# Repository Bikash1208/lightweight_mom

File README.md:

# HMSA Designer & RIS Metasurface Toolkit (`lwmom`)

A Python periodic Method-of-Moments solver for metasurface unit cells, plus a local web app ("HMSA Designer"):
- **HMSA Design:** Design holographic and reflectarray metasurface antennas end to end: upload a monopole feed's measured surface-wave field, configure multi-port beams and board geometry, synthesize holograms with sidelobe optimisation, predict far-field patterns, and export HFSS-ready CAD and AEDT scripts.
- **RIS Track (Phase 20):** Design 2-bit PIN-diode reconfigurable intelligent surfaces at X-band (10.5 GHz CP-2 Pancharatnam–Berry cell family and 1-bit LP interim), with plane-wave beam steering, coding synthesis, diode tolerance modeling, and board export.

Read **[docs/START_HERE.md](docs/START_HERE.md)** first — purpose, design flow, repo map,
conventions that bite.
Then **[docs/ROADMAP.md](docs/ROADMAP.md)** for deliverables, completed phases, and active track.
Check **[docs/STATUS.md](docs/STATUS.md)** for what's validated right now.

## Install and run

```bash
python3 --version                   # must be >= 3.11 -- if not, substitute your 3.11+
                                     # interpreter below (e.g. python3.12, python3.14, pyenv's)
python3 -m venv .venv && source .venv/bin/activate
pip install -e ".[dev,app,cad]"     # dev: tests/lint; app: the web app; cad: STEP export/plots
make app                            # starts the app at http://127.0.0.1:8000 -- restart after
                                     # any backend (src/) change, there is no autoreload
make test-fast                      # pytest -m "not slow", ~6-7 min
make test-full                      # everything, including real MoM solves, tens of minutes
make lint / make format             # ruff check(+format) / ruff check --fix + format
```

Python >= 3.11. `requirements-lock.txt` reproduces the exact pinned environment this project was
developed against (`pip install -r requirements-lock.txt`). See `docs/DEVELOPING.md` for the full
setup/test/lint walkthrough and `docs/ARCHITECTURE.md` for how the app is put together.

## More

- [docs/START_HERE.md](docs/START_HERE.md) — onboarding (humans and AI agents).
- [docs/ROADMAP.md](docs/ROADMAP.md) — planned deliverables, completed phases, and active milestones.
- [docs/STATUS.md](docs/STATUS.md) — current validation level per capability, open next steps.
- [docs/USER_GUIDE.md](docs/USER_GUIDE.md) — walkthrough of every app page.
- [docs/ARCHITECTURE.md](docs/ARCHITECTURE.md) — module map, data flow, job queue, storage.
- [docs/validation/README.md](docs/validation/README.md) — every validation run, with numbers.
- [docs/history/](docs/history/) — the full phase-by-phase project history.
- [jobs/README.md](jobs/README.md) — remote compute server job architecture and status matrix.
- [hfss_results/README.md](hfss_results/README.md) — external HFSS simulation runs and ground-truth data.
- [CHANGELOG.md](CHANGELOG.md), [CONTRIBUTING.md](CONTRIBUTING.md), [CLAUDE.md](CLAUDE.md).

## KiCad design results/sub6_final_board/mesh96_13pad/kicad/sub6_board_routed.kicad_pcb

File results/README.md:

# Results

Generated outputs, one folder per phase/script. Tracked research outputs (small
JSON/CSV/MD/plots/STEP) stay in git as the project's own record; a few genuinely heavy, fully
regenerable folders are gitignored (noted below).

| Folder | Produced by | Regenerate with |
|---|---|---|
| `phase8a_feasibility/` | Phase 8A feasibility gate | `scripts/research/run_phase8a_feasibility.py` |
| `phase8b_formulation/` | Phase 8B holographic formulation | `scripts/research/run_phase8b_formulation.py` |
| `phase8c_scattering/` | Phase 8C scattering architecture validation | `scripts/research/run_phase8c_validation.py` |
| `phase8e_control_bridge/` | Phase 8E control-variable bridge | `scripts/research/run_phase8e_control_bridge.py` |
| `phase9_validation/` | Phase 9 control-variable/local-periodicity validation | `scripts/research/run_phase9_validation.py` |
| `phase10_environment_model/` | Phase 10 environment-aware model | `scripts/research/run_phase10_environment_model.py` |
| `phase11_heterogeneous_mom/` | Phase 11 heterogeneous-MoM coupling study | `scripts/research/run_phase11_heterogeneous_mom.py` |
| `phase12a_ground_plane/` | Phase 12A PEC ground plane | `scripts/research/run_phase12a_ground_plane.py` |
| `phase12b_mesh_period_study/` | Phase 12B mesh/period study | `scripts/research/run_phase12b.py` |
| `phase12c_grounded_locality/`, `phase12c_hfss_export/` | Phase 12C grounded-supercell study + HFSS exports | `scripts/research/run_phase12c.py` |
| `phase12d_local_periodicity/` | Phase 12D step-limit + HFSS ingestion | `scripts/research/run_phase12d.py` |
| `phase13_part0/` | Phase 13 Part 0 carry-overs | `scripts/research/run_phase13_part0.py` |
| `validation_cases/` | Phase 6 STEP/JSON/CSV validation-case exports | `scripts/research/export_validation_cases.py` |
| `unit_cell_library/` | Phase 7 production unit-cell library | `examples/build_unit_cell_library.py` (long-running, resumable). **Gitignored**: `_solve/`, `database/`, `geometry/` (~554 MB) — only `manifest.json`/reports/plots are committed. |
| `nylon_cells_28ghz/` | Phase 19 Part B: 28 GHz nylon octagon cell library (RCWA, model-only) | `examples/build_nylon_cell_library_28ghz.py` (~3 min) |
| `transmitarray_dual30/` | Phase 19 Parts C-D: dual-beam ±30° nylon lens design, local-periodicity and error-bar records (model-only) | `scripts/research/phase19_design.py` (~15 min), then `phase19_local_periodicity.py` (~10 min); see its README |
| `phase20_r1_demo/` | Phase 20 R1: Oblique-incidence and lumped-load MoM demo outputs and convergence checks | `scripts/research/phase20_r1_demo.py` |
| `phase20_r2/` | Phase 20 R2: PIN diode circuit models (Skyworks SMP1345-079LF) and bias-dependent reflection sweeps | `scripts/research/phase20_r2_demo.py` |
| `phase20_r3/` | Phase 20 R3: 2-bit Pancharatnam-Berry octagon unit cell (CP-2) optimization, 4-state phase ladder, and supercell locality data | `scripts/research/phase20_r3_cp_package.py`, `scripts/research/phase20_r3_opt.py`, `scripts/research/phase20_r3_locality.py` |
| `phase20_r3b/` | Phase 20 R3b: Re-optimization study outcome; baseline CP-2 cell retained, optimisation stopped (`OUTCOME.md`) | `scripts/research/phase20_r3b_cp_package.py` |
| `phase20_r4/` | Phase 20 R4: Discrete state library (v1 and full-grid v2 at Floquet cutoff F = 2n = 120), cutoff audit, and HFSS compare plots. **Gitignored**: `chunks/` | `scripts/research/phase20_r4_build_library.py`, `scripts/research/phase20_r4_assemble.py`, `scripts/research/phase20_r4_hfss_compare.py` |
| `phase20_r5/` | Phase 20 R5: RIS design mode records, reference-plane calibration (`PLANE_CORRECTION.md`), R5-3 beam tables (`R5_3_REPORT.md`), and server MoM tolerance analysis (`TOLERANCE_GAP.md`) | `scripts/research/phase20_r5_rebuild_delta.py`, `scripts/research/phase20_r5_tolerance_mom.py`, `scripts/research/phase20_r5_tolerance_compare.py` |
| `phase23/` | Phase 23: square vs hexagon vs hexagon + sidelobe optimiser comparison on the held-out grid; the rectangle bit-identical gate | `scripts/research/phase23_compare_v2.py`; gate `scripts/research/phase23_rect_snapshot.py` |
| `phase25/` | Phase 25: Butler-fed sector scanner forward model (`forward_validation.json`), supercell locality checks, and aperture-taper sensitivity (model-only) | `scripts/research/phase25_forward_validation.py`, `scripts/research/phase25_locality_package.py`, `scripts/research/phase25_block_locality.py` |
| `phase26/` | Phase 26: Leakage-controlled tensor-CP hexagon design (`fourhex_A_cells.json`, `fourhex_B_cells.json`), launcher calibration, and substrate screening tables | `scripts/research/phase26_fourhex_design.py`, `scripts/research/phase26_launcher_package.py`, `scripts/research/phase26_substrate_study.py` |
| `infra/` | Server sync provenance records, mirror checks, and cross-machine equivalence artifacts | `scripts/research/equivalence_compare.py`, `scripts/research/phase20_r4_mirror_check.py` |
| `universal_database/` | Phase 8D-REV universal database architecture demo | `scripts/research/run_phase8d_rev_universal_database.py` |
| `hfss_compare_ledger.json` (not a folder) | Every HFSS-vs-MoM comparison run through the app's HFSS compare page | append-only; see `src/hfss_compare/service.py` |
| `submission_work/` | **Untracked scratch** (Oct 5–6 2026), not part of the repo | its reusable scripts moved to `scripts/adhoc/` in Phase 17; see that folder's own README |

Tests that read any of the folders above treat them as read-only fixtures/benchmarks — do not
hand-edit a results file to make a test pass; fix the generator or the test.

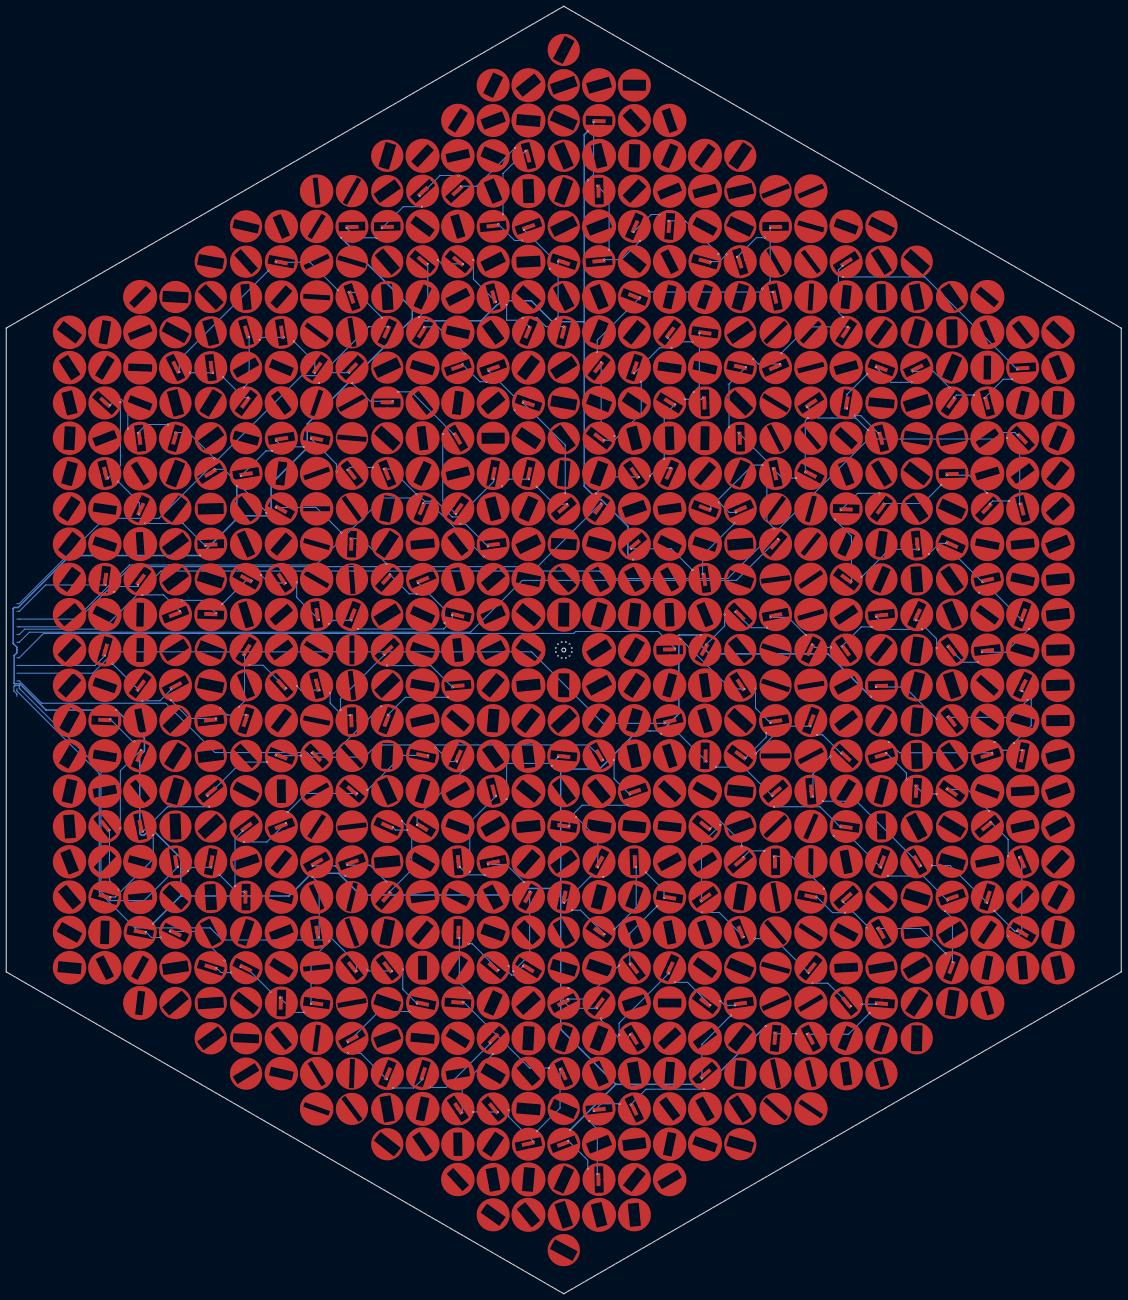
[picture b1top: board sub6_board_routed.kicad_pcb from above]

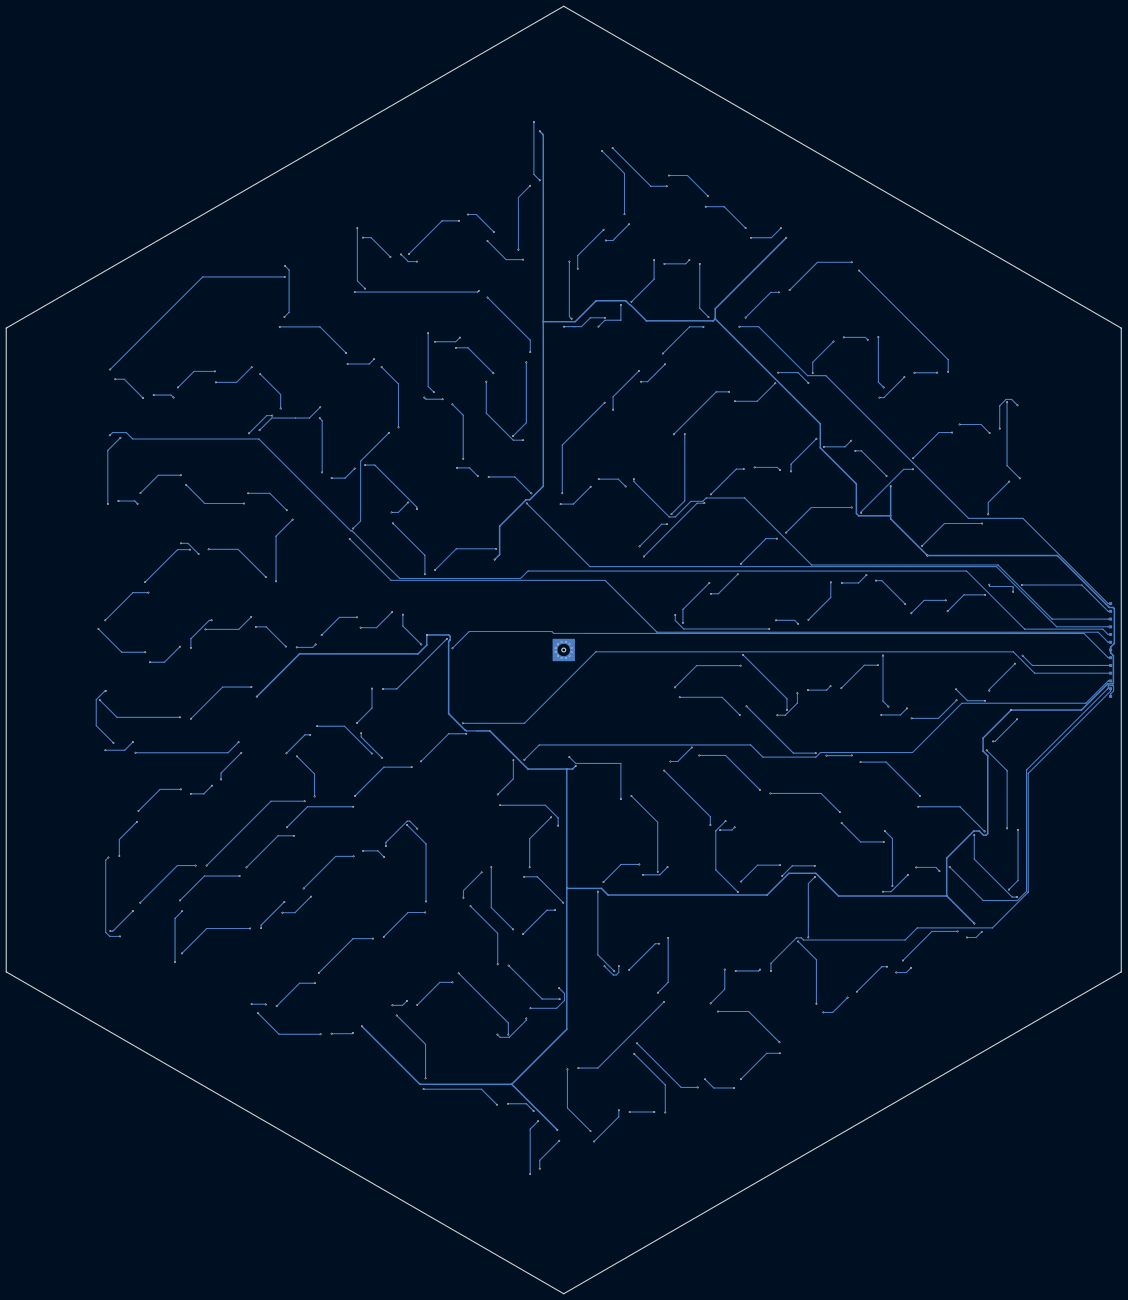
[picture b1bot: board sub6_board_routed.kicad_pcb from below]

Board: 4 copper layers, 366.4 x 423.1 mm, 1001 parts (2 on the bottom side), 241 nets.

Parts:
C0, C1, C2, C3, C4, C5, C6, C7, C8, C9, C10, C11, C12, C13, C14, C15, C16, C17, C18, C19, C20, C21, C22, C23, C24, C25, C26, C27, C28, C29, C30, C31, C32, C33, C34, C35, C36, C37, C38, C39, C40, C41, C42, C43, C44, C45, C46, C47, C48, C49, C50, C51, C52, C53, C54, C55, C56, C57, C58, C59, C60, C61, C62, C63, C64, C65, C66, C67, C68, C69, C70, C71, C72, C73, C74, C75, C76, C77, C78, C79, C80, C81, C82, C83, C84, C85, C86, C87, C88, C89, C90, C91, C92, C93, C94, C95, C96, C97, C98, C99, C100, C101, C102, C103, C104, C105, C106, C107, C108, C109, C110, C111, C112, C113, C114, C115, C116, C117, C118, C119, C120, C121, C122, C123, C124, C125, C126, C127, C128, C129, C130, C131, C132, C133, C134, C135, C136, C137, C138, C139, C140, C141, C142, C143, C144, C145, C146, C147, C148, C149, C150, C151, C152, C153, C154, C155, C156, C157, C158, C159, C160, C161, C162, C163, C164, C165, C166, C167, C168, C169, C170, C171, C172, C173, C174, C175, C176, C177, C178, C179, C180, C181, C182, C183, C184, C185, C186, C187, C188, C189, C190, C191, C192, C193, C194, C195, C196, C197, C198, C199, C200, C201, C202, C203, C204, C205, C206, C207, C208, C209, C210, C211, C212, C213, C214, C215, C216, C217, C218, C219, C220, C221, C222, C223, C224, C225, C226, C227, C228, C229, C230, C231, C232, C233, C234, C235, C236, C237, C238, C239, C240, C241, C242, C243, C244, C245, C246, C247, C248, C249, C250, C251, C252, C253, C254, C255, C256, C257, C258, C259, C260, C261, C262, C263, C264, C265, C266, C267, C268, C269, C270, C271, C272, C273, C274, C275, C276, C277, C278, C279, C280, C281, C282, C283, C284, C285, C286, C287, C288, C289, C290, C291, C292, C293, C294, C295, C296, C297, C298, C299, C300, C301, C302, C303, C304, C305, C306, C307, C308, C309, C310, C311, C312, C313, C314, C315, C316, C317, C318, C319, C320, C321, C322, C323, C324, C325, C326, C327, C328, C329, C330, C331, C332, C333, C334, C335, C336, C337, C338, C339, C340, C341, C342, C343, C344, C345, C346, C347, C348, C349, C350, C351, C352, C353, C354, C355, C356, C357, C358, C359, C360, C361, C362, C363, C364, C365, C366, C367, C368, C369, C370, C371, C372, C373, C374, C375, C376, C377, C378, C379, C380, C381, C382, C383, C384, C385, C386, C387, C388, C389, C390, C391, C392, C393, C394, C395, C396, C397, C398, C399, C400, C401, C402, C403, C404, C405, C406, C407, C408, C409, C410, C411, C412, C413, C414, C415, C416, C417, C418, C419, C420, C421, C422, C423, C424, C425, C426, C427, C428, C429, C430, C431, C432, C433, C434, C435, C436, C437, C438, C439, C440, C441, C442, C443, C444, C445, C446, C447, C448, C449, C450, C451, C452, C453, C454, C455, C456, C457, C458, C459, C460, C461, C462, C463, C464, C465, C466, C467, C468, C469, C470, C471, C472, C473, C474, C475, C476, C477, C478, C479, C480, C481, C482, C483, C484, C485, C486, C487, C488, C489, C490, C491, C492, C493, C494, C495, C496, C497, C498, C499, C500, C501, C502, C503, C504, C505, C506, C507, C508, C509, C510, C511, C512, C513, C514, C515, C516, C517, C518, C519, C520, C521, C522, C523, C524, C525, C526, C527, C528, C529, C530, C531, C532, C533, C534, C535, C536, C537, C538, C539, C540, C541, C542, C543, C544, C545, C546, C547, C548, C549, C550, C551, C552, C553, C554, C555, C556, C557, C558, C559, C560, C561, C562, C563, C564, C565, C566, C567, C568, C569, C570, C571, C572, C573, C574, C575, C576, C577, C578, C579, C580, C581, C582, C583, C584, C585, C586, C587, C588, C589, C590, C591, C592, C593, C594, C595, C596, C597, C598, C599, C600, C601, C602, C603, C604, C605, C606, C607, C608, C609, C610, C611, C612, C613, C614, C615, C616, C617, C618, C619, C620, C621, C622, C623, C624, C625, C626, C627, C628, C629, C630, C631, C632, C633, C634, C635, C636, C637, C638, C639, C640, C641, C642, C643, C644, C645, C646, C647, C648, C649, C650, C651, C652, C653, C654, C655, C656, C657, C658, C659, C660, C661, C662, C663, C664, C665, C666, C667, C668, C669, C670, C671, C672, C673, C674, C675, C676, C677, C678, C679, C680, C681, C682, C683, C684, C685, C686, C687, C688, C689, C690, C691, C692, C693, C694, C695, C696, C697, C698, C699, C700, C701, C702, C703, C704, C705, C706, C707, C708, C709, C710, C711, C712, C713, C714, C715, C716, C717, C718, C719, C720, C721, C722, C723, C724, C725, C726, C727, C728, C729, C730, C731, C732, C733, C734, C735, C736, C737, C738, C739, C740, C741, C742, C743, C744, C745, C746, C747, C748, C749, C750, C751, C752, C753, C754, C755, C756, C757: CELL
D1-01, D1-02, D1-03, D1-04, D1-05, D1-06, D1-07, D1-08, D1-09, D1-10, D1-11, D1-12, D1-13, D1-14, D1-15, D1-16, D1-17, D1-18, D1-19, D1-20, D2-01, D2-02, D2-03, D2-04, D2-05, D2-06, D2-07, D2-08, D2-09, D2-10, D2-11, D2-12, D2-13, D2-14, D2-15, D2-16, D2-17, D2-18, D2-19, D2-20, D3-01, D3-02, D3-03, D3-04, D3-05, D3-06, D3-07, D3-08, D3-09, D3-10, D3-11, D3-12, D3-13, D3-14, D3-15, D3-16, D3-17, D3-18, D3-19, D3-20, D4-01, D4-02, D4-03, D4-04, D4-05, D4-06, D4-07, D4-08, D4-09, D4-10, D4-11, D4-12, D4-13, D4-14, D4-15, D4-16, D4-17, D4-18, D4-19, D4-20, D5-01, D5-02, D5-03, D5-04, D5-05, D5-06, D5-07, D5-08, D5-09, D5-10, D5-11, D5-12, D5-13, D5-14, D5-15, D5-16, D5-17, D5-18, D5-19, D5-20, D6-01, D6-02, D6-03, D6-04, D6-05, D6-06, D6-07, D6-08, D6-09, D6-10, D6-11, D6-12, D6-13, D6-14, D6-15, D6-16, D6-17, D6-18, D6-19, D6-20, D7-01, D7-02, D7-03, D7-04, D7-05, D7-06, D7-07, D7-08, D7-09, D7-10, D7-11, D7-12, D7-13, D7-14, D7-15, D7-16, D7-17, D7-18, D7-19, D7-20, D8-01, D8-02, D8-03, D8-04, D8-05, D8-06, D8-07, D8-08, D8-09, D8-10, D8-11, D8-12, D8-13, D8-14, D8-15, D8-16, D8-17, D8-18, D8-19, D8-20, D9-01, D9-02, D9-03, D9-04, D9-05, D9-06, D9-07, D9-08, D9-09, D9-10, D9-11, D9-12, D9-13, D9-14, D9-15, D9-16, D9-17, D9-18, D9-19, D9-20, D10-01, D10-02, D10-03, D10-04, D10-05, D10-06, D10-07, D10-08, D10-09, D10-10, D10-11, D10-12, D10-13, D10-14, D10-15, D10-16, D10-17, D10-18, D10-19, D10-20, D11-01, D11-02, D11-03, D11-04, D11-05, D11-06, D11-07, D11-08, D11-09, D11-10, D11-11, D11-12, D11-13, D11-14, D11-15, D11-16, D11-17, D11-18, D11-19, D11-20, D12-01, D12-02, D12-03, D12-04, D12-05, D12-06, D12-07, D12-08, D12-09, D12-10, D12-11, D12-12, D12-13, D12-14, D12-15, D12-16, D12-17, D12-18, D12-19, D12-20: SC79
J1: EDGE_CONN13
J2: SMA_FLAT_PAD_6.35
P1: PROBE

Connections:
N01_01: C338.2, C366.1, D1-01.K, D1-02.A
N01_02: C338.1, C339.2, D1-02.K, D1-03.A
N01_03: C311.2, C339.1, D1-03.K, D1-04.A
N01_04: C311.1, C312.2, D1-04.K, D1-05.A
N01_05: C312.1, C370.2, D1-05.K, D1-06.A
N01_06: C342.2, C370.1, D1-06.K, D1-07.A
N01_07: C342.1, C343.2, D1-07.K, D1-08.A
N01_08: C315.2, C343.1, D1-08.K, D1-09.A
N01_09: C315.1, C374.2, D1-09.K, D1-10.A
N01_10: C347.2, C374.1, D1-10.K, D1-11.A
N01_11: C316.2, C347.1, D1-11.K, D1-12.A
N01_12: C285.2, C316.1, D1-12.K, D1-13.A
N01_13: C284.2, C285.1, D1-13.K, D1-14.A
N01_14: C253.2, C284.1, D1-14.K, D1-15.A
N01_15: C222.2, C253.1, D1-15.K, D1-16.A
N01_16: C163.2, C222.1, D1-16.K, D1-17.A
N01_17: C163.1, C221.2, D1-17.K, D1-18.A
N01_18: C221.1, C280.2, D1-18.K, D1-19.A
N01_19: C280.1, C308.2, D1-19.K, D1-20.A
N02_01: C194.1, C195.2, D2-01.K, D2-02.A
N02_02: C167.2, C195.1, D2-02.K, D2-03.A
N02_03: C167.1, C225.2, D2-03.K, D2-04.A
N02_04: C225.1, C226.2, D2-04.K, D2-05.A
N02_05: C226.1, C257.2, D2-05.K, D2-06.A
N02_06: C257.1, C288.2, D2-06.K, D2-07.A
N02_07: C288.1, C289.2, D2-07.K, D2-08.A
N02_08: C230.2, C289.1, D2-08.K, D2-09.A
N02_09: C229.2, C230.1, D2-09.K, D2-10.A
N02_10: C171.2, C229.1, D2-10.K, D2-11.A
N02_11: C171.1, C199.2, D2-11.K, D2-12.A
N02_12: C198.2, C199.1, D2-12.K, D2-13.A
N02_13: C140.2, C198.1, D2-13.K, D2-14.A
N02_14: C84.2, C140.1, D2-14.K, D2-15.A
N02_15: C83.2, C84.1, D2-15.K, D2-16.A
N02_16: C83.1, C109.2, D2-16.K, D2-17.A
N02_17: C108.2, C109.1, D2-17.K, D2-18.A
N02_18: C108.1, C136.2, D2-18.K, D2-19.A
N02_19: C135.2, C136.1, D2-19.K, D2-20.A
N03_01: C112.1, C113.2, D3-01.K, D3-02.A
N03_02: C87.2, C113.1, D3-02.K, D3-03.A
N03_03: C62.2, C87.1, D3-03.K, D3-04.A
N03_04: C43.2, C62.1, D3-04.K, D3-05.A
N03_05: C43.1, C44.2, D3-05.K, D3-06.A
N03_06: C44.1, C66.2, D3-06.K, D3-07.A
N03_07: C28.2, C66.1, D3-07.K, D3-08.A
N03_08: C28.1, C29.2, D3-08.K, D3-09.A
N03_09: C17.2, C29.1, D3-09.K, D3-10.A
N03_10: C17.1, C48.2, D3-10.K, D3-11.A
N03_11: C48.1, C88.2, D3-11.K, D3-12.A
N03_12: C88.1, C144.2, D3-12.K, D3-13.A
N03_13: C116.2, C144.1, D3-13.K, D3-14.A
N03_14: C116.1, C117.2, D3-14.K, D3-15.A
N03_15: C117.1, C175.2, D3-15.K, D3-16.A
N03_16: C175.1, C203.2, D3-16.K, D3-17.A
N03_17: C202.2, C203.1, D3-17.K, D3-18.A
N03_18: C202.1, C261.2, D3-18.K, D3-19.A
N03_19: C261.1, C292.2, D3-19.K, D3-20.A
N04_01: C265.2, C293.1, D4-01.K, D4-02.A
N04_02: C234.2, C265.1, D4-02.K, D4-03.A
N04_03: C206.2, C234.1, D4-03.K, D4-04.A
N04_04: C176.2, C206.1, D4-04.K, D4-05.A
N04_05: C148.2, C176.1, D4-05.K, D4-06.A
N04_06: C148.1, C207.2, D4-06.K, D4-07.A
N04_07: C179.2, C207.1, D4-07.K, D4-08.A
N04_08: C120.2, C179.1, D4-08.K, D4-09.A
N04_09: C91.2, C120.1, D4-09.K, D4-10.A
N04_10: C91.1, C92.2, D4-10.K, D4-11.A
N04_11: C70.2, C92.1, D4-11.K, D4-12.A
N04_12: C70.1, C121.2, D4-12.K, D4-13.A
N04_13: C95.2, C121.1, D4-13.K, D4-14.A
N04_14: C95.1, C96.2, D4-14.K, D4-15.A
N04_15: C52.2, C96.1, D4-15.K, D4-16.A
N04_16: C33.2, C52.1, D4-16.K, D4-17.A
N04_17: C32.2, C33.1, D4-17.K, D4-18.A
N04_18: C10.2, C32.1, D4-18.K, D4-19.A
N04_19: C10.1, C18.2, D4-19.K, D4-20.A
N05_01: C296.2, C324.1, D5-01.K, D5-02.A
N05_02: C269.2, C296.1, D5-02.K, D5-03.A
N05_03: C242.2, C269.1, D5-03.K, D5-04.A
N05_04: C214.2, C242.1, D5-04.K, D5-05.A
N05_05: C187.2, C214.1, D5-05.K, D5-06.A
N05_06: C129.2, C187.1, D5-06.K, D5-07.A
N05_07: C129.1, C156.2, D5-07.K, D5-08.A
N05_08: C156.1, C184.2, D5-08.K, D5-09.A
N05_09: C183.2, C184.1, D5-09.K, D5-10.A
N05_10: C183.1, C211.2, D5-10.K, D5-11.A
N05_11: C210.2, C211.1, D5-11.K, D5-12.A
N05_12: C210.1, C238.2, D5-12.K, D5-13.A
N05_13: C180.2, C238.1, D5-13.K, D5-14.A
N05_14: C152.2, C180.1, D5-14.K, D5-15.A
N05_15: C125.2, C152.1, D5-15.K, D5-16.A
N05_16: C99.2, C125.1, D5-16.K, D5-17.A
N05_17: C99.1, C100.2, D5-17.K, D5-18.A
N05_18: C75.2, C100.1, D5-18.K, D5-19.A
N05_19: C74.2, C75.1, D5-19.K, D5-20.A
N06_01: C355.2, C381.1, D6-01.K, D6-02.A
N06_02: C327.2, C355.1, D6-02.K, D6-03.A
N06_03: C297.2, C327.1, D6-03.K, D6-04.A
N06_04: C297.1, C328.2, D6-04.K, D6-05.A
N06_05: C300.2, C328.1, D6-05.K, D6-06.A
N06_06: C270.2, C300.1, D6-06.K, D6-07.A
N06_07: C215.2, C270.1, D6-07.K, D6-08.A
N06_08: C188.2, C215.1, D6-08.K, D6-09.A
N06_09: C160.2, C188.1, D6-09.K, D6-10.A
N06_10: C160.1, C218.2, D6-10.K, D6-11.A
N06_11: C218.1, C246.2, D6-11.K, D6-12.A
N06_12: C246.1, C274.2, D6-12.K, D6-13.A
N06_13: C273.2, C274.1, D6-13.K, D6-14.A
N06_14: C273.1, C301.2, D6-14.K, D6-15.A
N06_15: C301.1, C304.2, D6-15.K, D6-16.A
N06_16: C304.1, C305.2, D6-16.K, D6-17.A
N06_17: C305.1, C363.2, D6-17.K, D6-18.A
N06_18: C332.2, C363.1, D6-18.K, D6-19.A
N06_19: C332.1, C359.2, D6-19.K, D6-20.A
N07_01: C507.2, C565.1, D7-01.K, D7-02.A
N07_02: C506.2, C507.1, D7-02.K, D7-03.A
N07_03: C506.1, C534.2, D7-03.K, D7-04.A
N07_04: C503.2, C534.1, D7-04.K, D7-05.A
N07_05: C502.2, C503.1, D7-05.K, D7-06.A
N07_06: C444.2, C502.1, D7-06.K, D7-07.A
N07_07: C444.1, C475.2, D7-07.K, D7-08.A
N07_08: C475.1, C476.2, D7-08.K, D7-09.A
N07_09: C448.2, C476.1, D7-09.K, D7-10.A
N07_10: C420.2, C448.1, D7-10.K, D7-11.A
N07_11: C390.2, C420.1, D7-11.K, D7-12.A
N07_12: C389.2, C390.1, D7-12.K, D7-13.A
N07_13: C389.1, C417.2, D7-13.K, D7-14.A
N07_14: C416.2, C417.1, D7-14.K, D7-15.A
N07_15: C386.2, C416.1, D7-15.K, D7-16.A
N07_16: C385.2, C386.1, D7-16.K, D7-17.A
N07_17: C385.1, C413.2, D7-17.K, D7-18.A
N07_18: C412.2, C413.1, D7-18.K, D7-19.A
N07_19: C382.2, C412.1, D7-19.K, D7-20.A
N08_01: C471.1, C557.2, D8-01.K, D8-02.A
N08_02: C557.1, C615.2, D8-02.K, D8-03.A
N08_03: C615.1, C616.2, D8-03.K, D8-04.A
N08_04: C616.1, C647.2, D8-04.K, D8-05.A
N08_05: C647.1, C697.2, D8-05.K, D8-06.A
N08_06: C623.2, C697.1, D8-06.K, D8-07.A
N08_07: C593.2, C623.1, D8-07.K, D8-08.A
N08_08: C592.2, C593.1, D8-08.K, D8-09.A
N08_09: C592.1, C620.2, D8-09.K, D8-10.A
N08_10: C619.2, C620.1, D8-10.K, D8-11.A
N08_11: C589.2, C619.1, D8-11.K, D8-12.A
N08_12: C561.2, C589.1, D8-12.K, D8-13.A
N08_13: C561.1, C588.2, D8-13.K, D8-14.A
N08_14: C530.2, C588.1, D8-14.K, D8-15.A
N08_15: C529.2, C530.1, D8-15.K, D8-16.A
N08_16: C498.2, C529.1, D8-16.K, D8-17.A
N08_17: C498.1, C499.2, D8-17.K, D8-18.A
N08_18: C440.2, C499.1, D8-18.K, D8-19.A
N08_19: C440.1, C467.2, D8-19.K, D8-20.A
N09_01: C495.1, C525.2, D9-01.K, D9-02.A
N09_02: C525.1, C526.2, D9-02.K, D9-03.A
N09_03: C526.1, C584.2, D9-03.K, D9-04.A
N09_04: C584.1, C585.2, D9-04.K, D9-05.A
N09_05: C585.1, C643.2, D9-05.K, D9-06.A
N09_06: C642.2, C643.1, D9-06.K, D9-07.A
N09_07: C612.2, C642.1, D9-07.K, D9-08.A
N09_08: C553.2, C612.1, D9-08.K, D9-09.A
N09_09: C553.1, C611.2, D9-09.K, D9-10.A
N09_10: C611.1, C668.2, D9-10.K, D9-11.A
N09_11: C668.1, C672.2, D9-11.K, D9-12.A
N09_12: C672.1, C715.2, D9-12.K, D9-13.A
N09_13: C694.2, C715.1, D9-13.K, D9-14.A
N09_14: C693.2, C694.1, D9-14.K, D9-15.A
N09_15: C693.1, C712.2, D9-15.K, D9-16.A
N09_16: C711.2, C712.1, D9-16.K, D9-17.A
N09_17: C690.2, C711.1, D9-17.K, D9-18.A
N09_18: C690.1, C727.2, D9-18.K, D9-19.A
N09_19: C727.1, C749.2, D9-19.K, D9-20.A
N10_01: C521.1, C522.2, D10-01.K, D10-02.A
N10_02: C494.2, C522.1, D10-02.K, D10-03.A
N10_03: C494.1, C580.2, D10-03.K, D10-04.A
N10_04: C580.1, C608.2, D10-04.K, D10-05.A
N10_05: C607.2, C608.1, D10-05.K, D10-06.A
N10_06: C607.1, C635.2, D10-06.K, D10-07.A
N10_07: C635.1, C685.2, D10-07.K, D10-08.A
N10_08: C685.1, C686.2, D10-08.K, D10-09.A
N10_09: C664.2, C686.1, D10-09.K, D10-10.A
N10_10: C638.2, C664.1, D10-10.K, D10-11.A
N10_11: C638.1, C639.2, D10-11.K, D10-12.A
N10_12: C639.1, C689.2, D10-12.K, D10-13.A
N10_13: C689.1, C708.2, D10-13.K, D10-14.A
N10_14: C707.2, C708.1, D10-14.K, D10-15.A
N10_15: C707.1, C738.2, D10-15.K, D10-16.A
N10_16: C723.2, C738.1, D10-16.K, D10-17.A
N10_17: C722.2, C723.1, D10-17.K, D10-18.A
N10_18: C704.2, C722.1, D10-18.K, D10-19.A
N10_19: C703.2, C704.1, D10-19.K, D10-20.A
N11_01: C634.1, C660.2, D11-01.K, D11-02.A
N11_02: C660.1, C681.2, D11-02.K, D11-03.A
N11_03: C599.2, C681.1, D11-03.K, D11-04.A
N11_04: C599.1, C600.2, D11-04.K, D11-05.A
N11_05: C572.2, C600.1, D11-05.K, D11-06.A
N11_06: C572.1, C630.2, D11-06.K, D11-07.A
N11_07: C630.1, C631.2, D11-07.K, D11-08.A
N11_08: C603.2, C631.1, D11-08.K, D11-09.A
N11_09: C603.1, C604.2, D11-09.K, D11-10.A
N11_10: C576.2, C604.1, D11-10.K, D11-11.A
N11_11: C549.2, C576.1, D11-11.K, D11-12.A
N11_12: C491.2, C549.1, D11-12.K, D11-13.A
N11_13: C463.2, C491.1, D11-13.K, D11-14.A
N11_14: C463.1, C490.2, D11-14.K, D11-15.A
N11_15: C490.1, C518.2, D11-15.K, D11-16.A
N11_16: C517.2, C518.1, D11-16.K, D11-17.A
N11_17: C517.1, C545.2, D11-17.K, D11-18.A
N11_18: C544.2, C545.1, D11-18.K, D11-19.A
N11_19: C514.2, C544.1, D11-19.K, D11-20.A
N12_01: C423.1, C424.2, D12-01.K, D12-02.A
N12_02: C396.2, C424.1, D12-02.K, D12-03.A
N12_03: C396.1, C397.2, D12-03.K, D12-04.A
N12_04: C397.1, C427.2, D12-04.K, D12-05.A
N12_05: C427.1, C428.2, D12-05.K, D12-06.A
N12_06: C400.2, C428.1, D12-06.K, D12-07.A
N12_07: C400.1, C401.2, D12-07.K, D12-08.A
N12_08: C401.1, C404.2, D12-08.K, D12-09.A
N12_09: C404.1, C432.2, D12-09.K, D12-10.A
N12_10: C431.2, C432.1, D12-10.K, D12-11.A
N12_11: C431.1, C459.2, D12-11.K, D12-12.A
N12_12: C459.1, C486.2, D12-12.K, D12-13.A
N12_13: C486.1, C513.2, D12-13.K, D12-14.A
N12_14: C513.1, C541.2, D12-14.K, D12-15.A
N12_15: C540.2, C541.1, D12-15.K, D12-16.A
N12_16: C540.1, C568.2, D12-16.K, D12-17.A
N12_17: C510.2, C568.1, D12-17.K, D12-18.A
N12_18: C482.2, C510.1, D12-18.K, D12-19.A
N12_19: C455.2, C482.1, D12-19.K, D12-20.A
RETURN: C18.1, C74.1, C135.1, C292.1, C308.1, C359.1, C382.1, C455.1, C467.1, C514.1, C703.1, C749.1, D1-20.K, D2-20.K, D3-20.K, D4-20.K, D5-20.K, D6-20.K, D7-20.K, D8-20.K, D9-20.K, D10-20.K, D11-20.K, D12-20.K, J1.7
S01: C366.2, D1-01.A, J1.9
S02: C194.2, D2-01.A, J1.13
S03: C112.2, D3-01.A, J1.12
S04: C293.2, D4-01.A, J1.11
S05: C324.2, D5-01.A, J1.10
S06: C381.2, D6-01.A, J1.8
S07: C565.2, D7-01.A, J1.5
S08: C471.2, D8-01.A, J1.6
S09: C495.2, D9-01.A, J1.4
S10: C521.2, D10-01.A, J1.3
S11: C634.2, D11-01.A, J1.1
S12: C423.2, D12-01.A, J1.2
